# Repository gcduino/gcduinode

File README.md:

GCDuiNODE
=========

© 2014 Steve Dalton & Rod Christian

GCDuiNODE is a [GCDuino](https://github.com/gctechshop/gcduino) but running at 3.3V and includes a whole load of ports for  Networking modules. It was created by [Rod Christian](http://github.com/Rod-Refactor) and [Steve Dalton](http://github.com/spidie) of [Gold Coast TechSpace](http://gctechspace.org).

How to checkout this code
-------------------------

    git clone git@github.com:gctechshop/gcduinode.git

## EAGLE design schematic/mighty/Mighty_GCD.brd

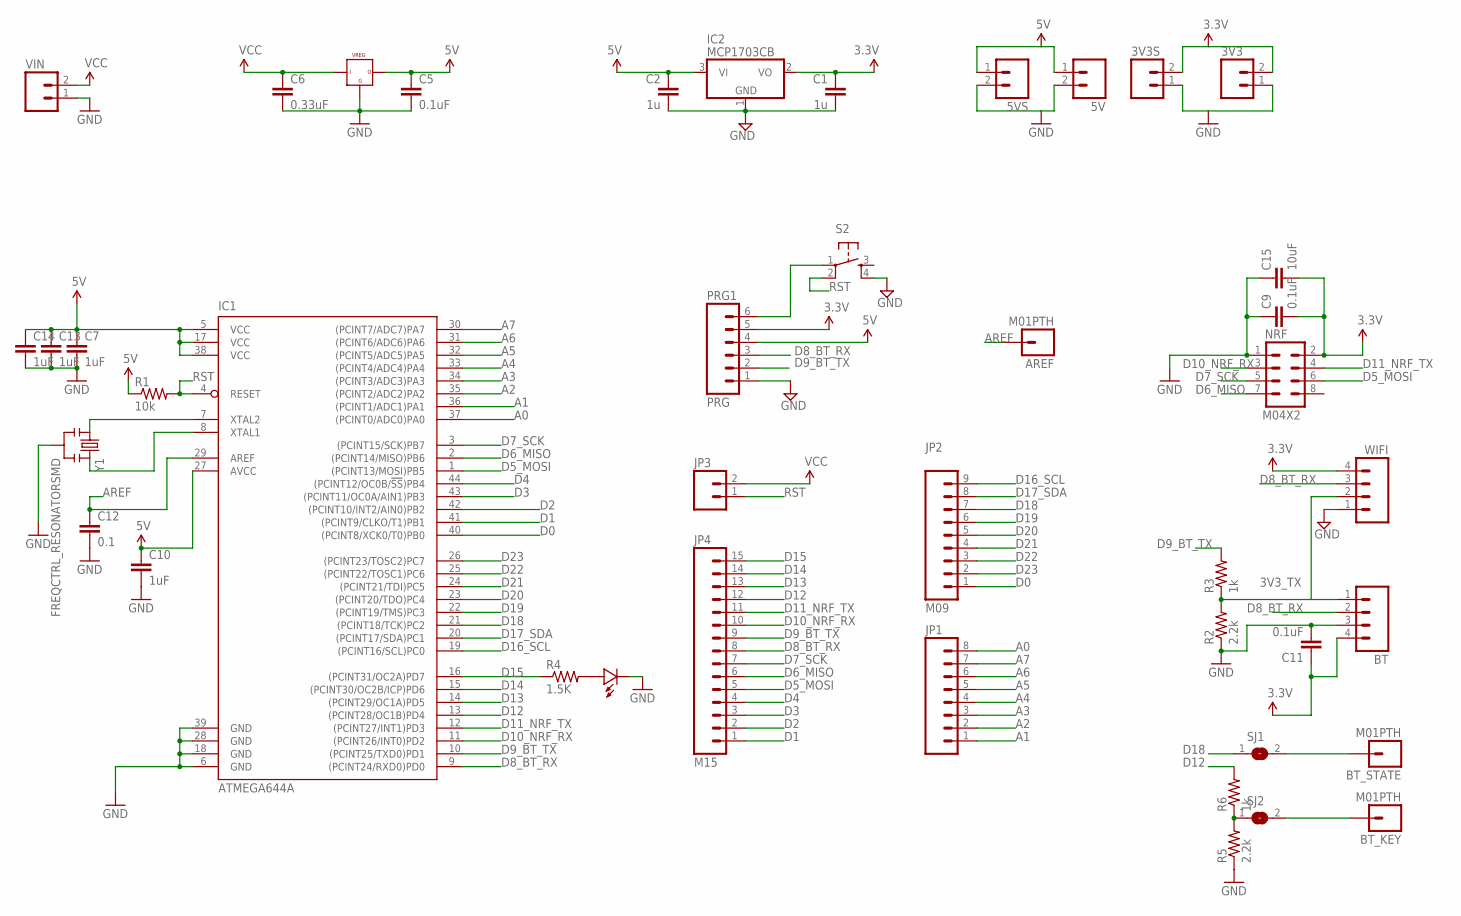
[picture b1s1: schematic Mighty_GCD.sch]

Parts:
3V3, 3V3S, 5V, 5VS: M02PTH; 1X02
AREF: M01PTH; 1X01
BT: M04PTH; 1X04
BT_KEY: M01PTH; 1X01
BT_STATE: M01PTH; 1X01
C1, C2: 1u; 0805
C5, C9, C11: 0.1uF; 0805
C6: 0.33uF; 0805
C7, C10, C13, C14: 1uF; 0805
C12: 0.1; 0805
C15: 10uF; 0805
IC1: ATMEGA644A; TQFP44
IC2: MCP1703CB; SOT23
JP1: M081X08; 1X08
JP2: M09; 1X09
JP3: M02PTH; 1X02
JP4: M15; 1X15
NRF: M04X2; 2X4
PRG1: PRG; 1X06
R1: 10k; 0805
R2, R5: 2.2k; 0805
R3, R6: 1k; 0805
R4: 1.5K; 0805
S2: TAC_SWITCHSMD; TACTILE_SWITCH_SMD
SJ1, SJ2: SJ
U$5: VREG_5V; DPACK
U$14: LED0805; 0805-LED
VIN: M02PTH; 1X02
WIFI: M04PTH; 1X04
Y1: FREQCTRL_RESONATORSMD; FREQCTRL_RESONATOR-SMD

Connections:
3.3V: 3V3.2, 3V3S.2, BT.4, C1.1, C9.2, C11.1, C15.2, IC2.2 (VO), NRF.2, PRG1.5, WIFI.4
3V3_TX: BT.1, R2.2, R3.1, WIFI.2
5V: 5V.1, 5VS.1, C2.1, C5.1, C7.1, C10.1, C13.1, C14.1, IC1.5 (VCC), IC1.17 (VCC), IC1.27 (AVCC), IC1.38 (VCC), IC2.3 (VI), PRG1.4, R1.1, U$5.3
A0: IC1.37 ((PCINT0/ADC0)PA0), JP1.8
A1: IC1.36 ((PCINT1/ADC1)PA1), JP1.1
A2: IC1.35 ((PCINT2/ADC2)PA2), JP1.2
A3: IC1.34 ((PCINT3/ADC3)PA3), JP1.3
A4: IC1.33 ((PCINT4/ADC4)PA4), JP1.4
A5: IC1.32 ((PCINT5/ADC5)PA5), JP1.5
A6: IC1.31 ((PCINT6/ADC6)PA6), JP1.6
A7: IC1.30 ((PCINT7/ADC7)PA7), JP1.7
AREF: AREF.1, C12.1, IC1.29 (AREF)
D0: IC1.40 ((PCINT8/XCK0/T0)PB0), JP2.1
D1: IC1.41 ((PCINT9/CLKO/T1)PB1), JP4.1
D2: IC1.42 ((PCINT10/INT2/AIN0)PB2), JP4.2
D3: IC1.43 ((PCINT11/OC0A/AIN1)PB3), JP4.3
D4: IC1.44 ((PCINT12/OC0B/!SS!)PB4), JP4.4
D5_MOSI: IC1.1 ((PCINT13/MOSI)PB5), JP4.5, NRF.6
D6_MISO: IC1.2 ((PCINT14/MISO)PB6), JP4.6, NRF.7
D7_SCK: IC1.3 ((PCINT15/SCK)PB7), JP4.7, NRF.5
D8_BT_RX: BT.2, IC1.9 ((PCINT24/RXD0)PD0), JP4.8, PRG1.3, WIFI.3
D9_BT_TX: IC1.10 ((PCINT25/TXD0)PD1), JP4.9, PRG1.2, R3.2
D10_NRF_RX: IC1.11 ((PCINT26/INT0)PD2), JP4.10, NRF.3
D11_NRF_TX: IC1.12 ((PCINT27/INT1)PD3), JP4.11, NRF.4
D12: IC1.13 ((PCINT28/OC1B)PD4), JP4.12, R6.2
D13: IC1.14 ((PCINT29/OC1A)PD5), JP4.13
D14: IC1.15 ((PCINT30/OC2B/ICP)PD6), JP4.14
D15: IC1.16 ((PCINT31/OC2A)PD7), JP4.15, R4.1
D16_SCL: IC1.19 ((PCINT16/SCL)PC0), JP2.9
D17_SDA: IC1.20 ((PCINT17/SDA)PC1), JP2.8
D18: IC1.21 ((PCINT18/TCK)PC2), JP2.7, SJ1.1
D19: IC1.22 ((PCINT19/TMS)PC3), JP2.6
D20: IC1.23 ((PCINT20/TDO)PC4), JP2.5
D21: IC1.24 ((PCINT21/TDI)PC5), JP2.4
D22: IC1.25 ((PCINT22/TOSC1)PC6), JP2.3
D23: IC1.26 ((PCINT23/TOSC2)PC7), JP2.2
GND: 3V3.1, 3V3S.1, 5V.2, 5VS.2, BT.3, C1.2, C2.2, C5.2, C6.2, C7.2, C9.1, C10.2, C11.2, C12.2, C13.2, C14.2, C15.1, IC1.6 (GND), IC1.18 (GND), IC1.28 (GND), IC1.39 (GND), IC2.1 (GND), NRF.1, PRG1.1, R2.1, R5.1, S2.4, U$5.2, U$14.MINUS, VIN.1, WIFI.1, Y1.2
unnamed: R4.2, U$14.PLUS
unnamed: IC1.7 (XTAL2), Y1.1
unnamed: IC1.8 (XTAL1), Y1.3
unnamed: PRG1.6, S2.1
unnamed: BT_STATE.1, SJ1.2
unnamed: BT_KEY.1, SJ2.2
unnamed: R5.2, R6.1, SJ2.1
RST: IC1.4 (RESET), JP3.1, R1.2, S2.2
VCC: C6.1, JP3.2, U$5.1, VIN.2

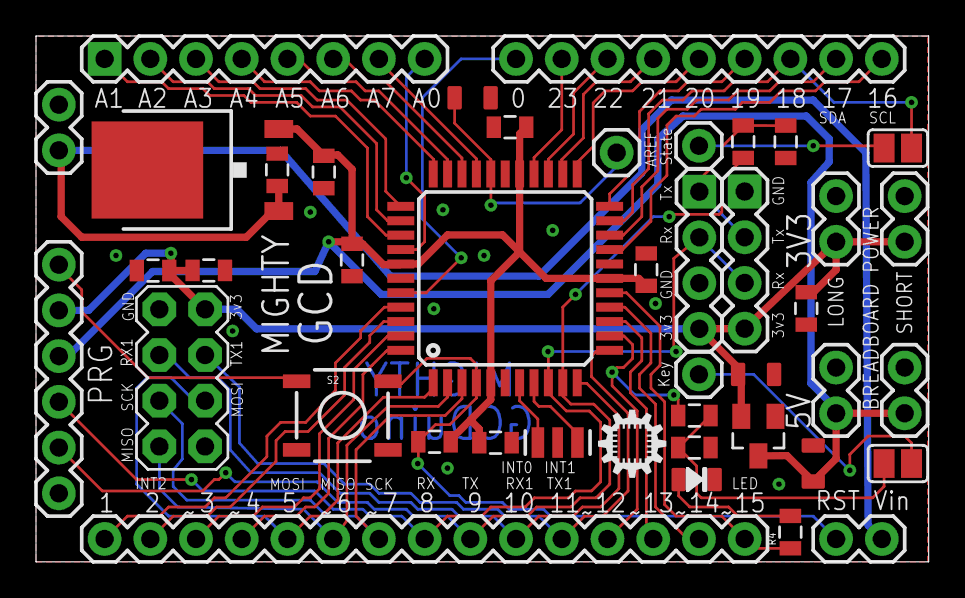
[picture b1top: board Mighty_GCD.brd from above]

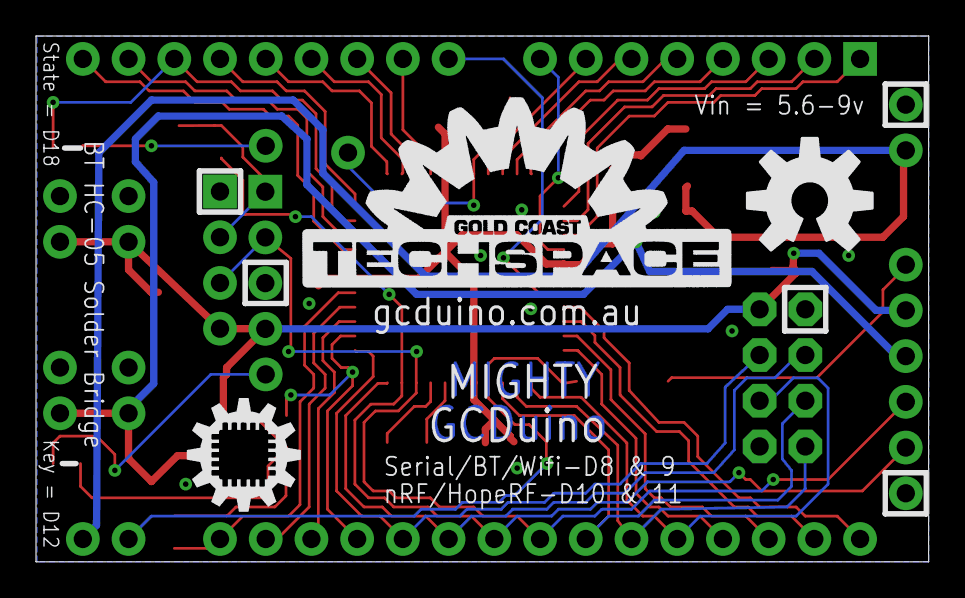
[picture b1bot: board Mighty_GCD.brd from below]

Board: 2 copper layers, 49.6 x 29.2 mm, 46 parts (3 on the bottom side), 46 nets.

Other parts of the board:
U$1: ID_LOGO_X0.25
U$2: GCTS_X0.5_TSILK
U$3: OSHW-LOGO-L
U$4: ID_LOGO_X0.15

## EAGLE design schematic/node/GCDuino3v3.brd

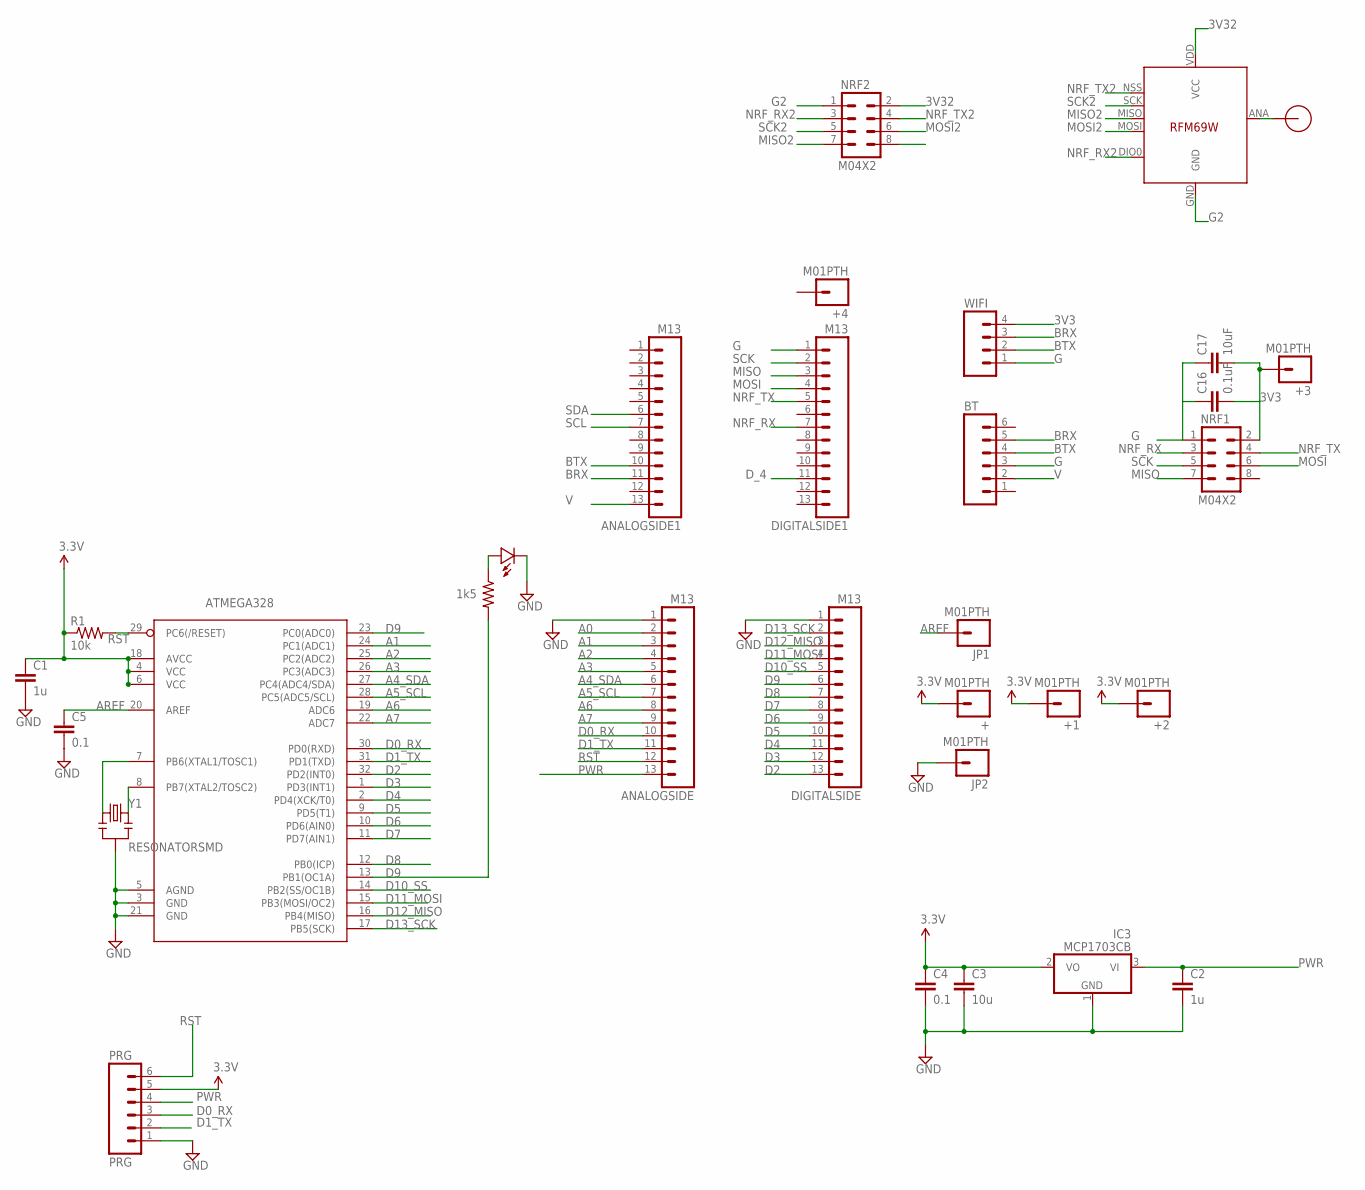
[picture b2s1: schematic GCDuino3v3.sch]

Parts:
+, +1, +2, +3, +4: M01PTH; 1X01
ANALOGSIDE, ANALOGSIDE1: M13; 1X13
ATMEGA328: ATMega-328; TQFP32-08
BT: M06SIP; 1X06
C1, C2: 1u; 0805
C3: 10u; 0805-CAP
C4, C5: 0.1; 0805
C16: 0.1uF; 0805
C17: 10uF; 0805
DIGITALSIDE, DIGITALSIDE1: M13; 1X13
IC3: MCP1703CB; SOT23
JP1, JP2: M01PTH; 1X01
NRF1, NRF2: M04X2; 2X4
PRG: PRG; 1X06
R1: 10k; 0805
R2: 1k5; 0805
U$2: LED0805; 0805-LED
U$5: RFM69; RFM69W-MINPADS
U$8: RFM12B_ANTENNA; RFM12B-ANTENNA
WIFI: M04PTH; 1X04
Y1: RESONATORSMD; RESONATOR-SMD

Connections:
3.3V: +.1, +1.1, +2.1, ATMEGA328.4 (VCC), ATMEGA328.6 (VCC), ATMEGA328.18 (AVCC), C1.1, C3.1, C4.1, IC3.2 (VO), PRG.5, R1.1
3V3: +3.1, C16.2, C17.2, NRF1.2, WIFI.4
3V32: NRF2.2, U$5.VDD (VCC)
A0: ANALOGSIDE.2, ATMEGA328.23 (PC0(ADC0))
A1: ANALOGSIDE.3, ATMEGA328.24 (PC1(ADC1))
A2: ANALOGSIDE.4, ATMEGA328.25 (PC2(ADC2))
A3: ANALOGSIDE.5, ATMEGA328.26 (PC3(ADC3))
A4_SDA: ANALOGSIDE.6, ATMEGA328.27 (PC4(ADC4/SDA))
A5_SCL: ANALOGSIDE.7, ATMEGA328.28 (PC5(ADC5/SCL))
A6: ANALOGSIDE.8, ATMEGA328.19 (ADC6)
A7: ANALOGSIDE.9, ATMEGA328.22 (ADC7)
AREF: ATMEGA328.20 (AREF), C5.1, JP1.1
BRX: ANALOGSIDE1.11, BT.5, WIFI.3
BTX: ANALOGSIDE1.10, BT.4, WIFI.2
D0_RX: ANALOGSIDE.10, ATMEGA328.30 (PD0(RXD)), PRG.3
D1_TX: ANALOGSIDE.11, ATMEGA328.31 (PD1(TXD)), PRG.2
D2: ATMEGA328.32 (PD2(INT0)), DIGITALSIDE.13
D3: ATMEGA328.1 (PD3(INT1)), DIGITALSIDE.12
D4: ATMEGA328.2 (PD4(XCK/T0)), DIGITALSIDE.11
D5: ATMEGA328.9 (PD5(T1)), DIGITALSIDE.10
D6: ATMEGA328.10 (PD6(AIN0)), DIGITALSIDE.9
D7: ATMEGA328.11 (PD7(AIN1)), DIGITALSIDE.8
D8: ATMEGA328.12 (PB0(ICP)), DIGITALSIDE.7
D9: ATMEGA328.13 (PB1(OC1A)), DIGITALSIDE.6, R2.2
D10_SS: ATMEGA328.14 (PB2(SS/OC1B)), DIGITALSIDE.5
D11_MOSI: ATMEGA328.15 (PB3(MOSI/OC2)), DIGITALSIDE.4
D12_MISO: ATMEGA328.16 (PB4(MISO)), DIGITALSIDE.3
D13_SCK: ATMEGA328.17 (PB5(SCK)), DIGITALSIDE.2
D_4: DIGITALSIDE1.11
G: BT.3, C16.1, C17.1, DIGITALSIDE1.1, NRF1.1, WIFI.1
G2: NRF2.1, U$5.GND
GND: ANALOGSIDE.1, ATMEGA328.3 (GND), ATMEGA328.5 (AGND), ATMEGA328.21 (GND), C1.2, C2.2, C3.2, C4.2, C5.2, DIGITALSIDE.1, IC3.1 (GND), JP2.1, PRG.1, U$2.MINUS, Y1.2
MISO: DIGITALSIDE1.3, NRF1.7
MISO2: NRF2.7, U$5.MISO
MOSI: DIGITALSIDE1.4, NRF1.6
MOSI2: NRF2.6, U$5.MOSI
unnamed: ATMEGA328.7 (PB6(XTAL1/TOSC1)), Y1.1
unnamed: R2.1, U$2.PLUS
unnamed: U$5.ANA (ANT), U$8.P$1
unnamed: ATMEGA328.8 (PB7(XTAL2/TOSC2)), Y1.3
NRF_RX: DIGITALSIDE1.7, NRF1.3
NRF_RX2: NRF2.3, U$5.DIO0
NRF_TX: DIGITALSIDE1.5, NRF1.4
NRF_TX2: NRF2.4, U$5.NSS (SEL)
PWR: ANALOGSIDE.13, C2.1, IC3.3 (VI), PRG.4
RST: ANALOGSIDE.12, ATMEGA328.29 (PC6(/RESET)), PRG.6, R1.2
SCK: DIGITALSIDE1.2, NRF1.5
SCK2: NRF2.5, U$5.SCK
SCL: ANALOGSIDE1.7
SDA: ANALOGSIDE1.6
V: ANALOGSIDE1.13, BT.2

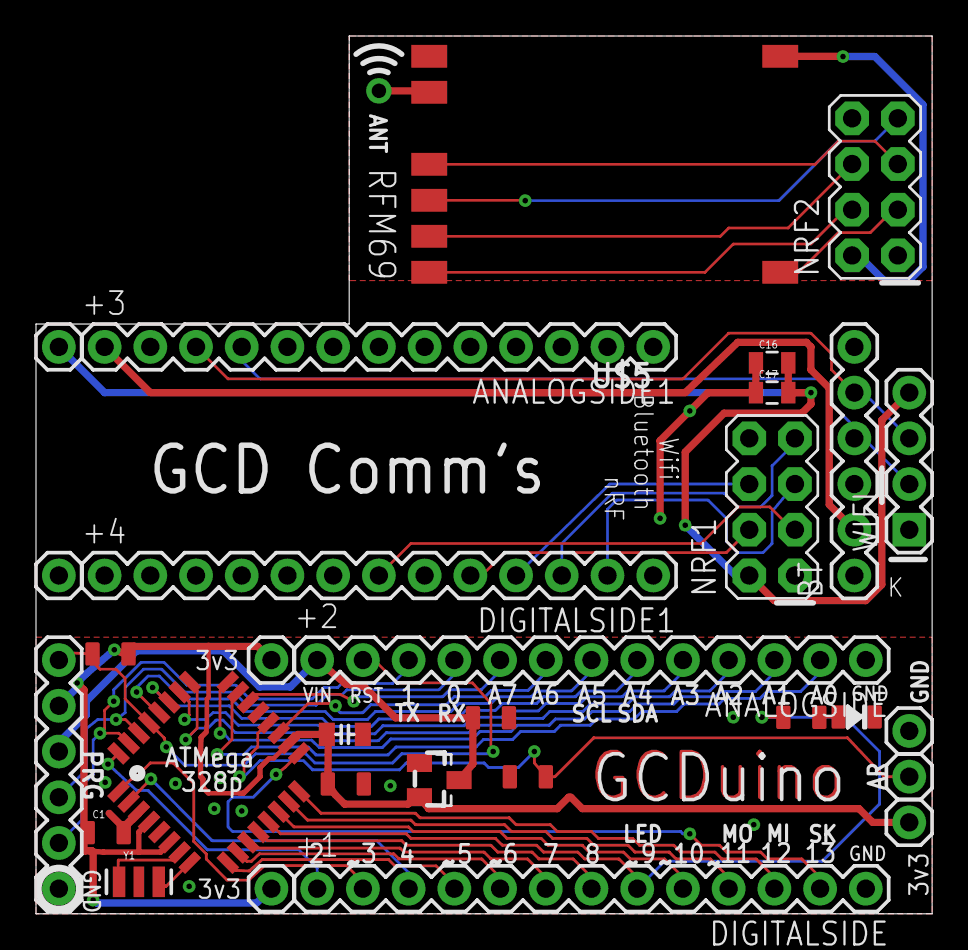
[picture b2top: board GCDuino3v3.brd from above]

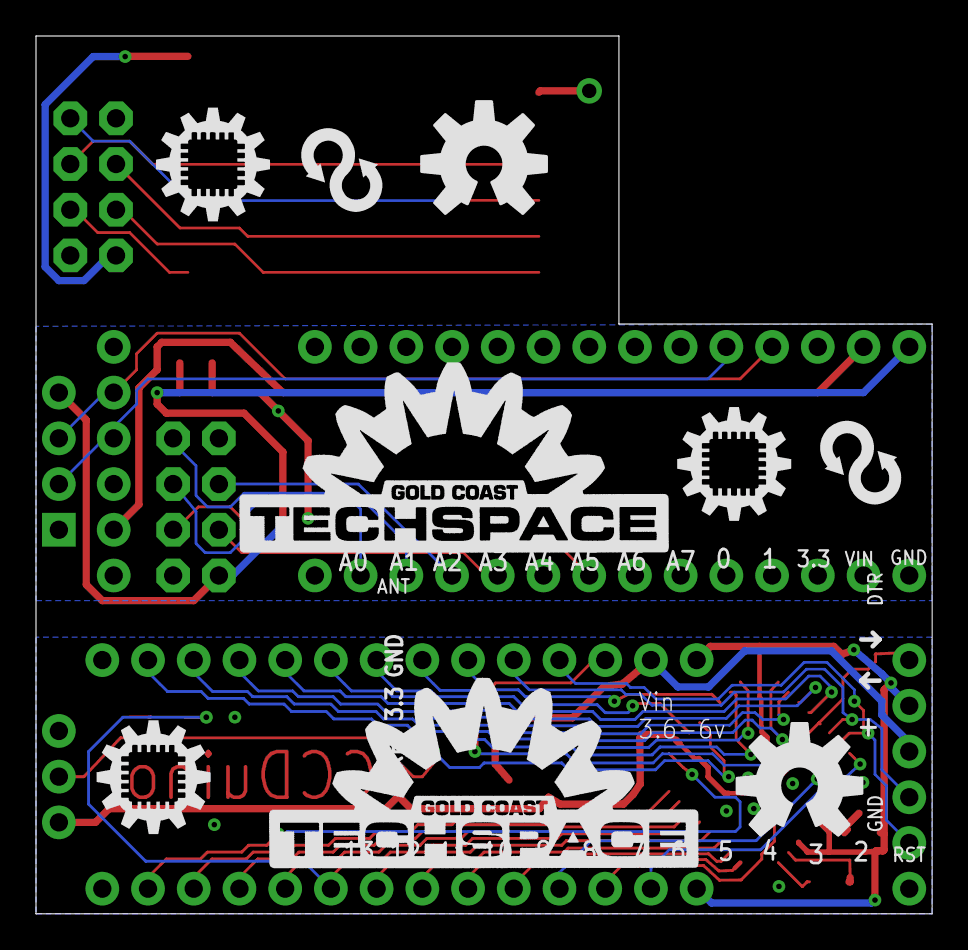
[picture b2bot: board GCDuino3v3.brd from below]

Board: 2 copper layers, 49.8 x 48.8 mm, 40 parts (9 on the bottom side), 48 nets.

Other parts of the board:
U$1, U$6, U$10: ID_LOGO_X0.25
U$3, U$12: REFACTORLOOP
U$4, U$9: GCTS_X0.5_TSILK
U$7, U$11: OSHW-LOGO-L

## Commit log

2014-03-21 added schematic
2014-03-21 added mighty
2014-03-24 Create RemoteGateSensor
2014-06-14 Added examples

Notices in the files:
parts and their libraries:
SparkFun-Resistors: Licensing: CC v3.0 Share-Alike You are welcome to use this library for commercial purposes.
